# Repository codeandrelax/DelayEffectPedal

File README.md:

# The Time Manipulator

This repository contains schematic, design files and firmware for digital delay guitar effect pedal based on PT2399.
Effect pedal was inspired by [_The Time Manipulator_](https://www.electrosmash.com/time-manipulator) effect pedal.

Electro Smash's pedal is built using popular Arduino ATMEGA328P-PU chip. 
Solution found in this repositroy doesn't use the same microcontroller. It uses PIC16F72.

Board is designed using surface mounted components (SMD).

Aditionaly, I have written on effect pedal design, it can be found in the repository [Analogna Efekt Pedala](./Analogna%20Efekt%20Pedala.pdf) (it's in Serbian)

## First version of the board

<table>
  <tr>
    <td></td>
    <td></td>
    <td></td>
  </tr>
  <tr>
    <td></td>
    <td></td>
    <td></td>
  </tr>
</table>

Firmware and PCB design of PT2399 IC based digital delay  effect guitar pedal

## Development diagram

## Render images

## Block diagram

## Schematics
[Schematics](PT2399_DigitalEffectPedal.pdf) PDF can be found in the repository. 

## Layout

Board dimensions are 75 mm by 78 mm.
Board layout is done as 4 layer board.

### Front Cu layer:

### In1. Cu layer:

### In2. Cu layer:
This layer has two power planes. Bigger one is for 5V supply, and the smaller one is for 9V supply.

### Back Cu layer:

## Firmawrae

## Tools

Tool used for schematics drwaing and pcb layout is [KiCad](https://www.kicad.org/), version 7.0.7

Tools used to draw block image is [ExcaliDraw](https://excalidraw.com/).

## TO DO

- Encoder board

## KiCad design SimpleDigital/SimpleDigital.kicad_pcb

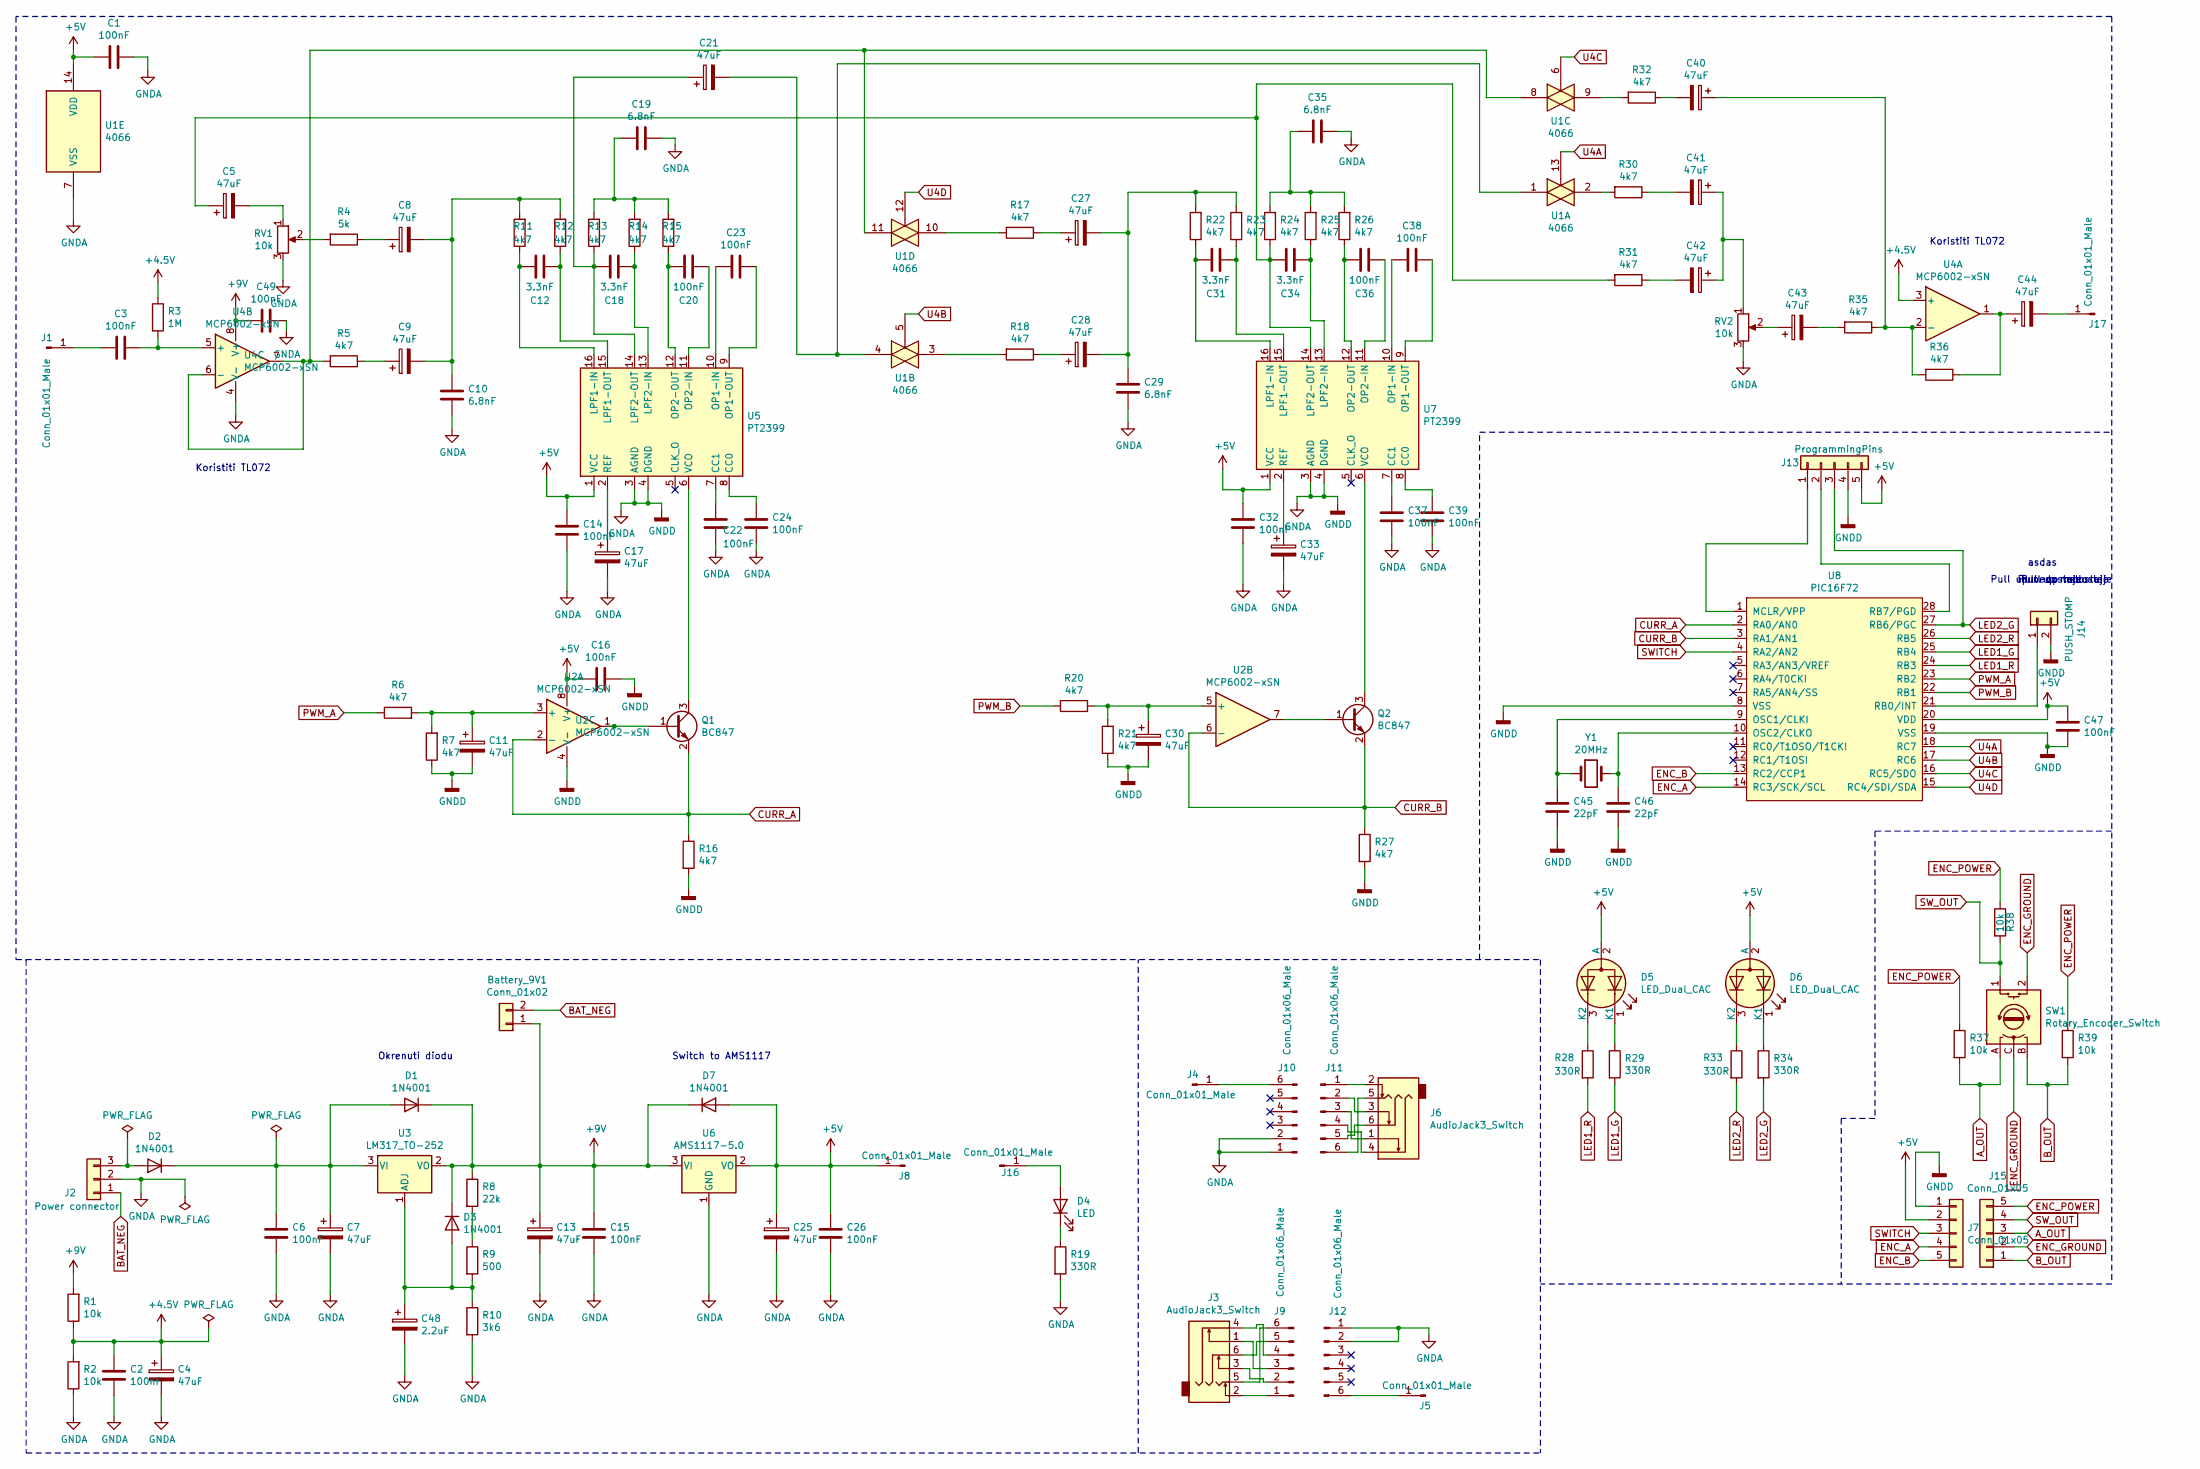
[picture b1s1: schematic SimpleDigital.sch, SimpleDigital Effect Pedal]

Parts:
Battery_9V1: Conn_01x02; Pin_Header_Straight_1x02_Pitch2.54mm
C1, C2, C3, C6, C14, C15, C16, C20, C22, C23, C24, C26, C32, C36, C37, C38, C39, C47, C49: 100nF; 0805
C4, C5, C7, C8, C9, C11, C13, C17, C21, C25, C27, C28, C30, C33, C40, C41, C42, C43, C44: 47uF; CP_Elec_5x5.3
C10, C19, C29, C35: 6.8nF; 0805
C12, C18, C31, C34: 3.3nF; 0805
C45, C46: 22pF; 0805
C48: 2.2uF; 0805
D1, D2, D3, D7: 1N4001; DO-214AC
D4: LED; LED_D5.0mm
D5, D6: LED_Dual_CAC; LED_D8.0mm-3
J1, J4, J5, J8, J16, J17: Conn_01x01_Male; Pin_d1.4mm_L8.5mm_W2.8mm_FlatFork
J2: Power connector; Pin_Header_Straight_1x03_Pitch2.54mm
J3, J6: AudioJack3_Switch; NMJ6HCD2
J7, J15: Conn_01x05; Pin_Header_Straight_1x05_Pitch2.54mm
J9, J10, J11, J12: Conn_01x06_Male; Pin_Header_Straight_1x06_Pitch2.54mm
J13: ProgrammingPins; Pin_Header_Straight_1x05_Pitch2.54mm
J14: PUSH_STOMP; Pin_Header_Straight_1x02_Pitch2.54mm
Q1, Q2: BC847; SOT-23-3
R1, R2, R37, R38, R39: 10k; 0805
R3: 1M; 0805
R4: 5k; 0805
R5, R6, R7, R11, R12, R13, R14, R15, R16, R17, R18, R20, R21, R22, R23, R24, R25, R26, R27, R30, R31, R32, R35, R36: 4k7; 0805
R8: 22k; 0805
R9: 500; 0805
R10: 3k6; 0805
R19, R28, R29, R33, R34: 330R; 0805
RV1, RV2: 10k; Potentiometer_WirePads_Small
SW1: Rotary_Encoder_Switch; Rotary_Encoder_Switched_PEC11R
U1: 4066; SOIC-14_W3.9mm
U2, U4: MCP6002-xSN; SOIC-8_W3.9mm
U3: LM317_TO-252; SOT-223
U5, U7: PT2399; SOIC-16_W3.90mm
U6: AMS1117-5.0; SOT-223
U8: PIC16F72; SOIC-28_W7.5mm
Y1: 20MHz; Crystal_SMD_HC49-SD_HandSoldering

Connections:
+4V: C2.2, C4.1, R1.1, R2.2, R3.1, U4.3 (+)
+5V: C1.2, C14.1, C16.2, C25.1, C26.2, C32.1, C47.2, D5.2 (A), D6.2 (A), D7.A, J7.2, J8.1, J13.5, U1.14 (VDD), U2.8 (V+), U5.1 (VCC), U6.2 (VO), U7.1 (VCC), U8.20 (VDD)
+9V: Battery_9V1.1, C13.1, C15.2, C49.2, D1.K, D3.K, D7.K, R1.2, R8.1, U3.2 (VO), U4.8 (V+), U6.3 (VI)
A_OUT: J15.3, R37.2, SW1.A
BAT_NEG: Battery_9V1.2, J2.1
B_OUT: J15.1, R39.2, SW1.B
CURR_A: Q1.2 (E), R16.1, U2.2 (-), U8.2 (RA0/AN0)
CURR_B: Q2.2 (E), R27.1, U2.6 (-), U8.3 (RA1/AN1)
ENC_A: J7.4, U8.14 (RC3/SCK/SCL)
ENC_B: J7.5, U8.13 (RC2/CCP1)
ENC_GROUND: J15.2, SW1.2 (S2), SW1.C
ENC_POWER: J15.5, R37.1, R38.1, R39.1
GNDA: C1.1, C2.1, C4.2, C6.1, C7.2, C10.2, C11.2, C13.2, C14.2, C15.1, C16.1, C17.2, C19.2, C22.1, C24.1, C25.2, C26.1, C29.2, C30.2, C32.2, C33.2, C35.2, C37.1, C39.1, C45.1, C46.1, C47.1, C48.2, C49.1, J2.2, J7.1, J10.1, J10.2, J12.1, J12.2, J13.4, J14.2, R2.1, R7.1, R10.2, R16.2, R19.2, R21.1, R27.2, RV1.3, RV2.3, U1.7 (VSS), U2.4 (V-), U4.4 (V-), U5.3 (AGND), U5.4 (DGND), U6.1 (GND), U7.3 (AGND), U7.4 (DGND), U8.8 (VSS), U8.19 (VSS)
LED1_G: R29.2, U8.25 (RB4)
LED1_R: R28.2, U8.24 (RB3)
LED2_G: J13.3, R34.2, U8.27 (RB6/PGC)
LED2_R: R33.2, U8.26 (RB5)
unnamed: C3.1, R3.2, U4.5 (+)
unnamed: C3.2, J1.1
unnamed: C5.2, RV1.1
unnamed: C6.2, C7.1, D1.A, D2.K, U3.3 (VI)
unnamed: C8.1, R4.1
unnamed: C9.1, R5.1
unnamed: C8.2, C9.2, C10.1, R11.2, R12.2
unnamed: C11.1, R6.2, R7.2, U2.3 (+)
unnamed: C12.1, R12.1, U5.15 (LPF1-OUT)
unnamed: C12.2, R11.1, U5.16 (LPF1-IN)
unnamed: C17.1, U5.2 (REF)
unnamed: C18.1, R14.1, U5.13 (LPF2-IN)
unnamed: C18.2, C21.1, R13.1, U5.14 (LPF2-OUT)
unnamed: C19.1, R13.2, R14.2, R15.2
unnamed: C20.1, U5.11 (OP2-IN)
unnamed: C20.2, R15.1, U5.12 (OP2-OUT)
unnamed: C21.2, U1.1, U1.4
unnamed: C22.2, U5.7 (CC1)
unnamed: C23.1, U5.9 (OP1-OUT)
unnamed: C23.2, U5.10 (OP1-IN)
unnamed: C24.2, U5.8 (CC0)
unnamed: C27.1, R17.1
unnamed: C27.2, C28.2, C29.1, R22.2, R23.2
unnamed: C28.1, R18.1
unnamed: C30.1, R20.2, R21.2, U2.5 (+)
unnamed: C31.1, R23.1, U7.15 (LPF1-OUT)
unnamed: C31.2, R22.1, U7.16 (LPF1-IN)
unnamed: C33.1, U7.2 (REF)
unnamed: C34.1, R25.1, U7.13 (LPF2-IN)
unnamed: C5.1, C34.2, R24.1, R31.2, U7.14 (LPF2-OUT)
unnamed: C35.1, R24.2, R25.2, R26.2
unnamed: C36.1, U7.11 (OP2-IN)
unnamed: C36.2, R26.1, U7.12 (OP2-OUT)
unnamed: C37.2, U7.7 (CC1)
unnamed: C38.1, U7.9 (OP1-OUT)
unnamed: C38.2, U7.10 (OP1-IN)
unnamed: C39.2, U7.8 (CC0)
unnamed: C40.1, R35.1, R36.2, U4.2 (-)
unnamed: C40.2, R32.1
unnamed: C41.1, C42.1, RV2.1
unnamed: C41.2, R30.1
unnamed: C42.2, R31.1
unnamed: C43.1, RV2.2
unnamed: C43.2, R35.2
unnamed: C44.1, R36.1, U4.1
unnamed: C44.2, J17.1
unnamed: C45.2, U8.9 (OSC1/CLKI), Y1.1
unnamed: C46.2, U8.10 (OSC2/CLKO), Y1.2
unnamed: C48.1, D3.A, R9.2, R10.1, U3.1 (ADJ)
unnamed: D2.A, J2.3
unnamed: D4.1 (K), R19.1
unnamed: D4.2 (A), J16.1
unnamed: D5.1 (K1), R29.1
unnamed: D5.3 (K2), R28.1
unnamed: D6.1 (K1), R34.1
unnamed: D6.3 (K2), R33.1
unnamed: J3.1, J9.3
unnamed: J3.2, J9.1
unnamed: J3.3, J9.2
unnamed: J3.4, J9.4
unnamed: J3.5, J9.6
unnamed: J3.6, J9.5
unnamed: J4.1, J10.6
unnamed: J6.2, J11.1
unnamed: J6.3, J11.2
unnamed: J6.1, J11.3
unnamed: J6.4, J11.4
unnamed: J6.6, J11.5
unnamed: J6.5, J11.6
unnamed: J5.1, J12.6
unnamed: J13.1, U8.1 (MCLR/VPP)
unnamed: J13.2, U8.28 (RB7/PGD)
unnamed: J14.1, U8.21 (RB0/INT)
unnamed: Q1.1 (B), U2.1
unnamed: Q1.3 (C), U5.6 (VCO)
unnamed: Q2.1 (B), U2.7
unnamed: Q2.3 (C), U7.6 (VCO)
unnamed: R4.2, RV1.2
unnamed: R5.2, U1.8, U1.11, U4.6 (-), U4.7
unnamed: R8.2, R9.1
unnamed: R17.2, U1.10
unnamed: R18.2, U1.3
unnamed: R30.2, U1.2
unnamed: R32.2, U1.9
PWM_A: R6.1, U8.23 (RB2)
PWM_B: R20.1, U8.22 (RB1)
SWITCH: J7.3, U8.4 (RA2/AN2)
SW_OUT: J15.4, R38.2, SW1.1 (S1)
U4A: U1.13, U8.18 (RC7)
U4B: U1.5, U8.17 (RC6)
U4C: U1.6, U8.16 (RC5/SDO)
U4D: U1.12, U8.15 (RC4/SDI/SDA)

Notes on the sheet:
Switch to AMS1117
Okrenuti diodu
Pull up nedostaje
asdas
Pull up nedostaje
Koristiti TL072

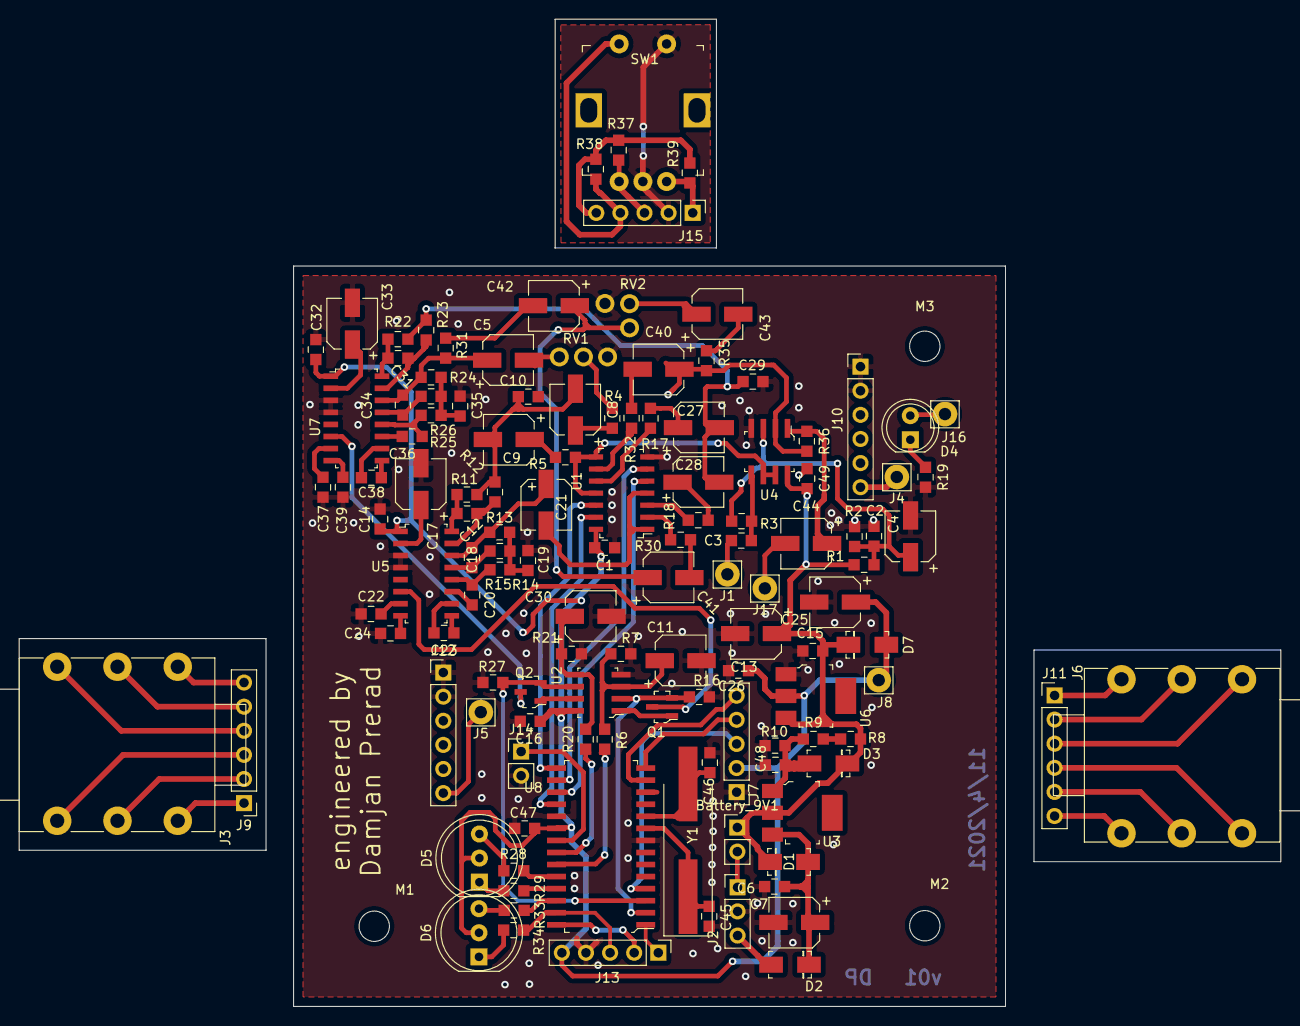
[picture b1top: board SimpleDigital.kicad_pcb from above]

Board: 2 copper layers, 75.0 x 78.0 mm, 130 parts (0 on the bottom side), 109 nets.

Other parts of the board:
M1, M2, M3: MountingHole_3.2mm_M3

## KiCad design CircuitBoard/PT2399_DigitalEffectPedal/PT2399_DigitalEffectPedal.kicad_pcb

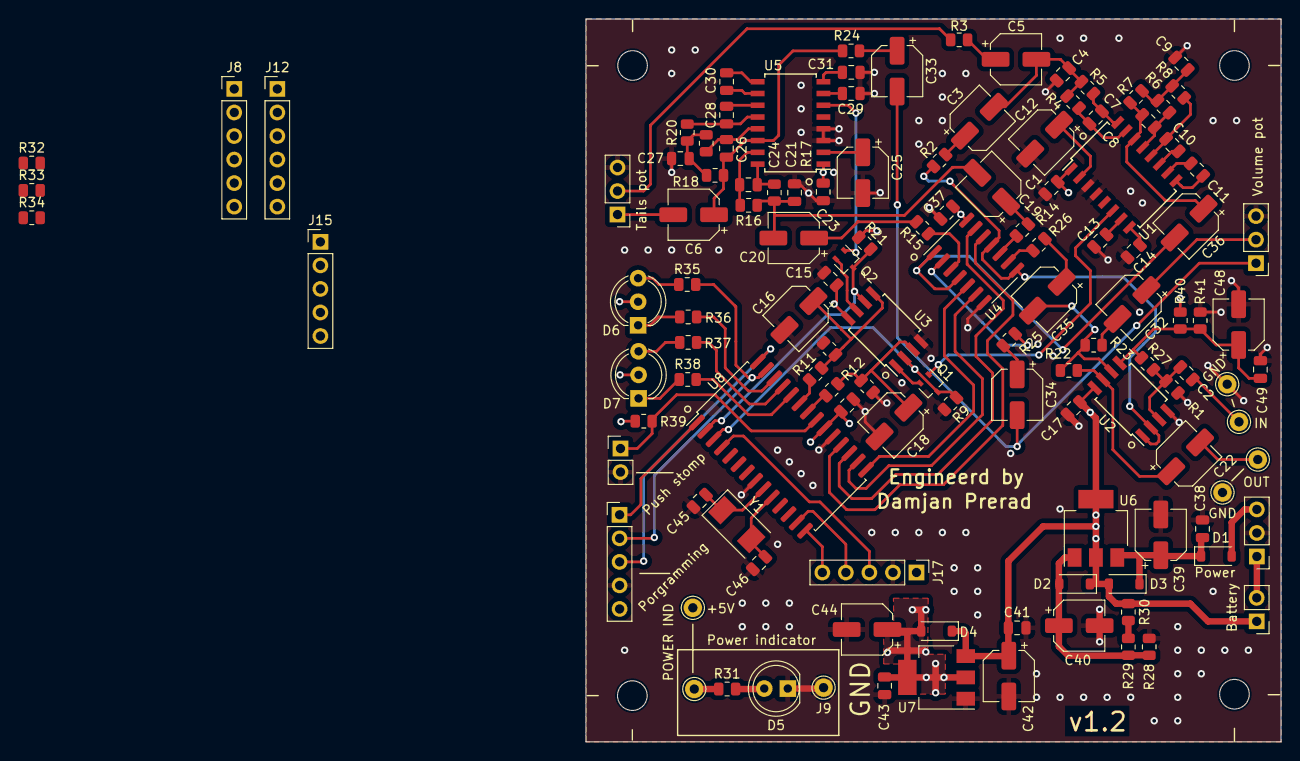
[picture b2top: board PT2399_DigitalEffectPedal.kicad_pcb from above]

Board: 4 copper layers, 75.0 x 78.0 mm, 130 parts (1 on the bottom side), 94 nets.

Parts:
 : MountingHole; MountingHole_3.2mm_M3
 #2,  #3,  #4: MountingHole; MountingHole_3.2mm_M3
 #5: POWER_SOURCE; Pin_D1.0mm_L10.0mm
 #6: LOGO
Battery: Battery_9V; PinHeader_1x02_P2.54mm_Vertical
C1, C2, C10, C11, C13, C14, C15, C17, C23, C28, C29, C30, C31, C37, C38, C41, C43, C47, C49: 100n; C_0805_2012Metric
C3, C5, C6, C12, C16, C18, C19, C20, C22, C25, C32, C33, C34, C35, C36, C39, C40, C42, C44, C48: 47uF; CP_Elec_5x5.3
C4, C21: 6n8; C_0805_2012Metric
C7, C8, C9, C24, C26, C27: 3n3; C_0805_2012Metric
C45, C46: 22p; C_0805_2012Metric
D1, D2, D3, D4: 1N4001; D_SOD-123
D5: LED; LED_D5.0mm
D6, D7: LED_Dual_KAK; LED_D5.0mm-3
GND: 3PDT_AudioInput; Pin_D1.0mm_L10.0mm
GND#2: 3PDT_AudioIOutput; Pin_D1.0mm_L10.0mm
IN: SIG_INPUT_STOMP; Pin_D1.0mm_L10.0mm
J8: AudioInput_connector; PinHeader_1x06_P2.54mm_Vertical
J9: GND_POWER_INDICATOR; Pin_D1.0mm_L10.0mm
J12: AudioOutput_connector; PinHeader_1x06_P2.54mm_Vertical
J15: Encoder_connector; PinHeader_1x05_P2.54mm_Vertical
J17: Encoder_board_connector; PinHeader_1x05_P2.54mm_Vertical
OUT: SIG_OUTPUT_STOMP; Pin_D1.0mm_L10.0mm
POWER IND: POWER_INDICATOR; Pin_D1.0mm_L10.0mm
Porgramming: Programming header; PinHeader_1x05_P2.54mm_Vertical
Power: Power connector; PinHeader_1x03_P2.54mm_Vertical
Push stomp: PUSH_STOMP; PinHeader_1x02_P2.54mm_Vertical
Q1, Q2: BC547; SOT-323_SC-70
R1, R27: 1 Meg; R_0805_2012Metric
R2, R4, R5, R6, R7, R8, R9, R10, R11, R12, R13, R14, R15, R16, R17, R18, R19, R20, R21, R22, R23, R24, R25, R26: 4k7; R_0805_2012Metric
R3: 5k; R_0805_2012Metric
R28: 3k6; R_0805_2012Metric
R29: 500; R_0805_2012Metric
R30: 22k; R_0805_2012Metric
R31: 33OR; R_0805_2012Metric
R32, R33, R34, R39, R40, R41: 10k; R_0805_2012Metric
R35, R36, R37, R38: 330R; R_0805_2012Metric
Tails pot: 10k; PinHeader_1x03_P2.54mm_Vertical
U1, U5: PT2399; SOIC-16W_5.3x10.2mm_P1.27mm
U2, U3: MCP6002-xSN; SOIC-8W_5.3x5.3mm_P1.27mm
U4: 4066; SOIC-14_3.9x8.7mm_P1.27mm
U6: LM317_SOT-223; SOT-223-3_TabPin2
U7: AMS1117-5.0; SOT-223-3_TabPin2
U8: PIC16F72; SOIC-28W_7.5x17.9mm_P1.27mm
Volume pot: 10k; PinHeader_1x03_P2.54mm_Vertical
Y1: Crystal; Crystal_SMD_0603-2Pin_6.0x3.5mm

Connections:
+4.5V: C48.1, C49.1, R27.1, R40.2, R41.1, U2.5 (+)
+5V: #5.1, C1.1, C15.1, C23.1, C37.1, C43.1, C44.1, C47.1, D4.2 (A), D6.2 (A), D7.2 (A), J17.1, Porgramming.5, R39.1, R40.1, U1.1 (VCC), U3.8 (V+), U4.14 (VDD), U5.1 (VCC), U7.2 (VO), U8.20 (VDD)
+9V: Battery.1, C17.1, C41.1, C42.1, D2.1 (K), D3.2 (A), D4.1 (K), R30.1, U2.8 (V+), U6.2 (VO), U7.3 (VI)
A_OUT: J15.5, R33.2
BAT_NEG: Battery.2, Power.1
B_OUT: J15.1, R32.2
CURR_A: Q2.3 (E), R21.1, U3.6 (-), U8.2 (RA0/AN0)
CURR_B: Q1.3 (E), R9.1, U3.2 (-), U8.3 (RA1/AN1)
ENC_A: J17.4, U8.13 (RC2/CCP1)
ENC_B: J17.5, U8.14 (RC3/SCK/SCL)
ENC_POWER: J15.3, R32.1, R33.1, R34.1
GNDA: C1.2, C4.2, C9.1, C12.2, C13.2, C14.2, C15.2, C16.2, C17.2, C18.2, C21.2, C23.2, C25.2, C27.1, C29.2, C31.2, C37.2, C38.2, C39.2, C40.2, C41.2, C42.2, C43.2, C44.2, C45.2, C46.2, C47.2, C48.2, C49.2, D5.1 (K), GND.1, GND#2.1, J9.1, J17.2, Porgramming.4, Power.2, Push stomp.2, R1.2, R9.2, R10.2, R13.2, R21.2, R28.2, R41.2, Tails pot.3, U1.3 (AGND), U1.4 (DGND), U2.4 (V-), U3.4 (V-), U4.7 (VSS), U5.3 (AGND), U5.4 (DGND), U7.1 (GND), U8.8 (VSS), U8.19 (VSS), Volume pot.3
LED1_G: R36.2, U8.26 (RB5)
LED1_R: Porgramming.2, R35.2, U8.27 (RB6/PGC)
LED2_G: R38.2, U8.24 (RB3)
LED2_R: R37.2, U8.25 (RB4)
MCLR: Porgramming.1, U8.1 (MCLR/VPP)
unnamed: C3.1, R2.2
unnamed: C3.2, C4.1, C5.2, R4.1, R5.1
unnamed: C5.1, R3.2
unnamed: C6.2, Tails pot.1
unnamed: C9.2, R6.1, R7.1, R8.1
unnamed: C19.1, R14.2
unnamed: C19.2, C20.2, C21.1, R16.1, R17.1
unnamed: C20.1, R15.2
unnamed: C22.1, R22.2, U2.7
unnamed: C27.2, R18.1, R19.1, R20.1
unnamed: C32.1, Volume pot.2
unnamed: C32.2, R23.1
unnamed: C33.1, R24.2
unnamed: C33.2, C34.2, Volume pot.1
unnamed: C34.1, R25.2
unnamed: C35.1, R26.2
unnamed: C36.2, U4.1, U4.4
unnamed: D1.2 (A), Power.3
unnamed: C38.1, C39.1, D1.1 (K), D3.1 (K), U6.3 (VI)
unnamed: C40.1, D2.2 (A), R28.1, R29.2, U6.1 (ADJ)
unnamed: D5.2 (A), R31.2
unnamed: D6.1 (K1), R36.1
unnamed: D6.3 (K2), R35.1
unnamed: D7.1 (K1), R38.1
unnamed: D7.3 (K2), R37.1
unnamed: POWER IND.1, R31.1
unnamed: Porgramming.3, U8.28 (RB7/PGD)
unnamed: Push stomp.1, R39.2, U8.21 (RB0/INT)
unnamed: Q1.2 (B), U3.1
unnamed: Q1.1 (C), U1.6 (VCO)
unnamed: Q2.2 (B), U3.7
unnamed: Q2.1 (C), U5.6 (VCO)
unnamed: R3.1, Tails pot.2
unnamed: R14.1, U4.10
unnamed: R15.1, U4.3
unnamed: R25.1, U4.2
unnamed: R26.1, U4.9
unnamed: R29.1, R30.2
unnamed: C14.1, U1.8 (CC0)
unnamed: C13.1, U1.7 (CC1)
unnamed: C7.1, R5.2, U1.16 (LPF1-IN)
unnamed: C7.2, R4.2, U1.15 (LPF1-OUT)
unnamed: C8.2, R6.2, U1.13 (LPF2-IN)
unnamed: C8.1, C36.1, R7.2, U1.14 (LPF2-OUT)
unnamed: C11.2, U1.10 (OP1-IN)
unnamed: C11.1, U1.9 (OP1-OUT)
unnamed: C10.1, U1.11 (OP2-IN)
unnamed: C10.2, R8.2, U1.12 (OP2-OUT)
unnamed: C12.1, U1.2 (REF)
unnamed: C2.2, R1.1, R27.2, U2.3 (+)
unnamed: R2.1, U2.1, U2.2 (-), U4.8, U4.11
unnamed: C35.2, R22.1, R23.2, U2.6 (-)
unnamed: C18.1, R12.1, R13.1, U3.3 (+)
unnamed: C16.1, R10.1, R11.1, U3.5 (+)
unnamed: C31.1, U5.8 (CC0)
unnamed: C29.1, U5.7 (CC1)
unnamed: C24.1, R17.2, U5.16 (LPF1-IN)
unnamed: C24.2, R16.2, U5.15 (LPF1-OUT)
unnamed: C26.2, R19.2, U5.13 (LPF2-IN)
unnamed: C6.1, C26.1, R18.2, R24.1, U5.14 (LPF2-OUT)
unnamed: C30.2, U5.10 (OP1-IN)
unnamed: C30.1, U5.9 (OP1-OUT)
unnamed: C28.1, U5.11 (OP2-IN)
unnamed: C28.2, R20.2, U5.12 (OP2-OUT)
unnamed: C25.1, U5.2 (REF)
unnamed: C45.1, U8.9 (OSC1/CLKI), Y1.1
unnamed: C46.1, U8.10 (OSC2/CLKO), Y1.2
PBTN: J17.3, U8.4 (RA2/AN2)
PB_OUT: J15.4, R34.2
PWM_A: R11.2, U8.23 (RB2)
PWM_B: R12.2, U8.22 (RB1)
SIG_IN: C2.1, IN.1
SIG_OUT: C22.2, OUT.1
U4A: U4.13, U8.17 (RC6)
U4B: U4.5, U8.15 (RC4/SDI/SDA)
U4C: U4.6, U8.16 (RC5/SDO)
U4D: U4.12, U8.18 (RC7)

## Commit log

2024-09-01 Schematics done, pcb layout needs to be done as well as firmware for control section
2024-09-10 PCB layout
2024-09-10 Layout PCB
2024-09-14 PCB layout - main part
2024-09-14 Some warningss and errors fixed, added silk screen block diagram
2024-09-14 Minor estetic changes to board layout
2024-09-14 Minor estetic changes
2024-09-14 Analgna efekt pedala pdf added
2024-09-21 Added GND vias to connect power planes
2024-09-27 Added earlier version, from couple of years ago
